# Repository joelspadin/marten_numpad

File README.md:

# Marten Numpad

Marten 22 is a wireless, 21/22 key numpad named after a [cute, woodland animal](https://en.wikipedia.org/wiki/American_marten). (There is no meaning to the name other than that I like them, and I couldn't find any existing keyboards named after them.) It is based on the nRF52840 SoC and uses a 3D printed case.

It has the following features:

- USB and Bluetooth support with [ZMK Firmware](https://zmk.dev/)
- Hot swap sockets for MX switches
- Supports Li-Ion or LiPo batteries up to 68x40x8 mm or 55x44x8 mm.
- The top-left and top-right keys can be replaced with encoders.
  - Supports [SKYLOONG keyboard knobs](https://skyloongtech.com/skyloong-keyboard-knobs/) (silicone cover versions only) or a separate encoder PCB with 3D printed case
- Any pair of two keys on the top row can be replaced with a display.
  - This uses a separate display PCB and connects with a ribbon cable.
  - nice!view and SSD1306 OLED display modules are supported.

A 22/23 key layout with a split plus key would be possible, but it would require a separate PCB from the 21/22 key layout. There is no way to fit three hot swap sockets into the space for the plus key without rotating the 1U keys 90 degrees, and this could damage keycaps, so I opted not to include that as an option.

(TODO: add renders/pictures of the completed keyboard)

> ⚠️ WARNING ⚠️ </br>
> I have received PCBs but they have not been fully tested. You should probably not make one yourself until I verify that everything works.

**Hardware status:**

| Component                | Status   |
| ------------------------ | -------- |
| Numpad PCB               | Untested |
| nice!view display module | Untested |
| OLED display module      | Untested |
| Encoder module           | Untested |
| 3D printed case          | Untested |

**Firmware status:**

| Component             | Status          |
| --------------------- | --------------- |
| Base firmware         | Not implemented |
| Numlock LED           | Not implemented |
| Custom display screen | Not implemented |
| nPM1300 charger       | Not implemented |
| nPM1300 fuel gauge    | Not implemented |
| Power button          | Not implemented |

## PCB

KiCad files for the PCBs can be found in the [pcb](./pcb) directory. There are a few PCBs:

- [numpad.kicad_pro](./pcb/numpad.kicad_pro) is the main PCB.
- [display.kicad_pro](./pcb/display.kicad_pro) is an optional daughterboard for connecting a [nice!view](https://nicekeyboards.com/nice-view/) display.
- [display_oled.kicad_pro](./pcb/display_oled.kicad_pro) is an optional daughterboard for connect an SSD1306 OLED display.
  - It works with the common SSD1306 display modules you can find from a wide variety of sellers, but make sure to get one which does _not_ have a pin header already soldered.
- [encoder.kicad_pro](./pcb/encoder.kicad_pro) is an optional daughterboard for an EC11 encoder.
- [peripheral.kicad_pro](./pcb/peripheral.kicad_pro) is template for creating your own daughterboards.

The main PCB requires a couple of parts which are not hand solderable, so PCB assembly is required.

The display and encoder PCBs are hand solderable (though the SMD parts on the encoder are difficult to solder). The encoder PCB also requires modifying the EC11 encoder by clipping its pins short.

Instructions for ordering and assembling the hardware will be found on the wiki, once I finish writing them. (TODO: add a wiki page)

[PCBWay](https://www.pcbway.com/) provided me a discount on PCB assembly in exchange for [sharing pictures of the completed board and talking about my experience ordering from them](https://github.com/joelspadin/marten_numpad/wiki/PCBWay-Assembly).

### Custom Peripherals

The numpad PCB has a [Molex 5051100692](https://www.molex.com/en-us/products/part-detail/5051100692) FFC connector (labeled "Display") which can be used to connect to a daughterboard using a 6-pin ribbon cable. It provides 3.3 V power, two ground pins, and three GPIO pins. While its main purpose is to connect a display, you can use this to add your own custom hardware as well.

(TODO: add a wiki page explaining custom hardware and firmware)

## Case

TODO

## Firmware

TODO

## Credits

- Fonts:
  - [Fredoka](https://fonts.google.com/specimen/Fredoka)
- Libraries:
  - [marbastlib](https://github.com/ebastler/marbastlib)
  - Some footprints are modified from the [KiCad Libraries](https://gitlab.com/kicad/libraries/kicad-footprints)
- 3D models
  - Some 3D models are generated using [KiCad Packages3D Generator](https://gitlab.com/kicad/libraries/kicad-packages3D-generator)
  - [128x32 OLED display](https://grabcad.com/library/0-91-128x32-oled-display-1)
  - [JST SH connector](https://grabcad.com/library/jst-sh-smd-connectors-1)
  - Models for the following parts are provided by their respective manufacturers:
    - [Bourns PEC11L](https://www.bourns.com/products/encoders/contacting-encoders/product/PEC11L)
    - [HRO TYPE-C-31-M-12](https://www.snapeda.com/parts/TYPE-C-31-M-12/HRO%20Electronics%20Co.,%20Ltd./view-part/)
    - [Kingbright APTR3216-VFX](https://www.kingbrightusa.com/product.asp?catalog_name=LED&product_id=APTR3216-VFX)
    - [Molex 781710002](https://www.molex.com/en-us/products/part-detail/781710002)
    - [Molex 5051100692](https://www.molex.com/en-us/products/part-detail/5051100692)
    - [Mill-Max 811-22-002-30-004101](https://www.mill-max.com/products/spring-loaded/pogo-pin-header-strip/811/30-004101/811-22-002-30-004101)
    - [Mill-Max 811-22-004-30-001101](https://www.mill-max.com/products/spring-loaded/pogo-pin-header-strip/811/30-001101/811-22-004-30-001101)
    - [Mill-Max 821-22-005-10-001101](https://www.mill-max.com/products/spring-loaded/pogo-pin-header-strip/821/10-001101/821-22-005-10-001101)
    - [Raytac MDBT50Q-1MV2](https://www.raytac.com/product/ins.php?index_id=24)
    - [Würth 9774005243R](https://www.we-online.com/en/components/products/SMSI_SMT_STEEL_SPACER_M2_THREAD_INTERNAL)

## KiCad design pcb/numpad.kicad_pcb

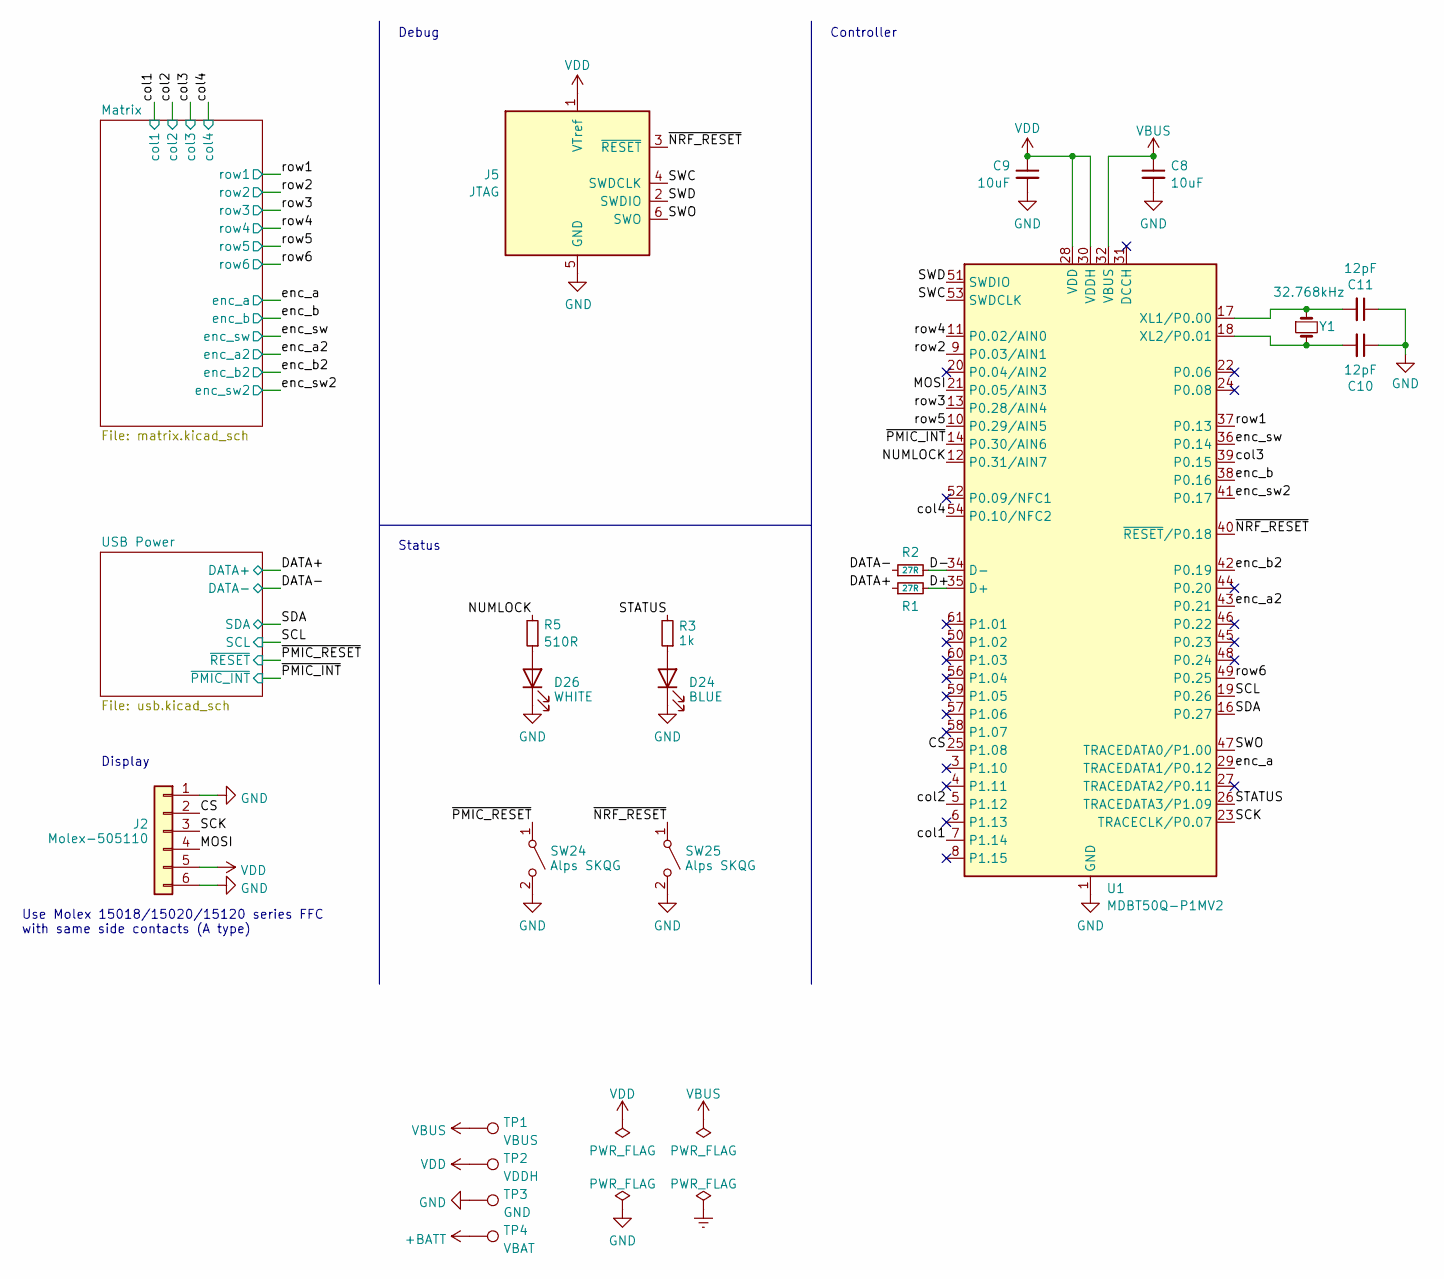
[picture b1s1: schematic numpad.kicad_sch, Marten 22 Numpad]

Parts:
C8, C9: 10uF; C_0603_1608Metric; Manufacturer Part Number GRM188Z71A106KA73D
C10, C11: 12pF; C_0402_1005Metric; Manufacturer Part Number CC0402GRNPO9BN120
D24: BLUE; LED_0603_1608Metric; Manufacturer Part Number NCD0603B5
D26: WHITE; LED_1206_3216Metric_ReverseMount_Hole2x2mm; Manufacturer Part Number MHT151WDT
J2: Molex-505110; Molex_5051100692_1x06_P0.5mm_Anchor; Manufacturer Part Number 5051100692
J5: JTAG; Tag-Connect_TC2030-IDC-NL_2x03_P1.27mm_Vertical; Manufacturer Part Number DNP
R1, R2: 27R; R_0402_1005Metric; Manufacturer Part Number RC0402FR-0727RL
R3: 1k; R_0603_1608Metric; Manufacturer Part Number FRC0603J102 TS
R5: 510R; R_0603_1608Metric; Manufacturer Part Number FRC0603J471 TS
SW24: Alps SKQG; SW_SPST_SKQG_WithStem; Manufacturer Part Number SKQGADE010
SW25: Alps SKQG; SW_SPST_SKQG_WithStem; Manufacturer Part Number SKQGABE010
TP1: VBUS; TestPoint_Pad_D1.5mm; Manufacturer Part Number DNP
TP2: VDDH; TestPoint_Pad_D1.5mm; Manufacturer Part Number DNP
TP3: GND; TestPoint_Pad_D1.5mm; Manufacturer Part Number DNP
TP4: VBAT; TestPoint_Pad_D1.5mm; Manufacturer Part Number DNP
U1: MDBT50Q-P1MV2; Raytac_MDBT50Q; Manufacturer Part Number MDBT50Q-P1MV2
Y1: 32.768kHz; Crystal_SMD_3215-2Pin_3.2x1.5mm; Manufacturer Part Number SC-32S32.768kHz20PPM9pF

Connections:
+BATT: TP4.1; also elsewhere on the board
/CS: J2.2, U1.25 (P1.08)
/D+: R1.2, U1.35 (D+)
/D-: R2.2, U1.34 (D-)
/DATA+: R1.1; also elsewhere on the board
/DATA-: R2.1; also elsewhere on the board
/MOSI: J2.4, U1.21 (P0.05/AIN3)
/NUMLOCK: R5.2, U1.12 (P0.31/AIN7)
/SCK: J2.3, U1.23 (TRACECLK/P0.07)
/SCL: U1.19 (P0.26); also elsewhere on the board
/SDA: U1.16 (P0.27); also elsewhere on the board
/STATUS: R3.2, U1.26 (TRACEDATA3/P1.09)
/SWC: J5.4 (SWDCLK), U1.53 (SWDCLK)
/SWD: J5.2 (SWDIO), U1.51 (SWDIO)
/SWO: J5.6 (SWO), U1.47 (TRACEDATA0/P1.00)
/col1: U1.7 (P1.14); also elsewhere on the board
/col2: U1.5 (P1.12); also elsewhere on the board
/col3: U1.39 (P0.15); also elsewhere on the board
/col4: U1.54 (P0.10/NFC2); also elsewhere on the board
/enc_a: U1.29 (TRACEDATA1/P0.12); also elsewhere on the board
/enc_a2: U1.43 (P0.21); also elsewhere on the board
/enc_b: U1.38 (P0.16); also elsewhere on the board
/enc_b2: U1.42 (P0.19); also elsewhere on the board
/enc_sw: U1.36 (P0.14); also elsewhere on the board
/enc_sw2: U1.41 (P0.17); also elsewhere on the board
/row1: U1.37 (P0.13); also elsewhere on the board
/row2: U1.9 (P0.03/AIN1); also elsewhere on the board
/row3: U1.13 (P0.28/AIN4); also elsewhere on the board
/row4: U1.11 (P0.02/AIN0); also elsewhere on the board
/row5: U1.10 (P0.29/AIN5); also elsewhere on the board
/row6: U1.49 (P0.25); also elsewhere on the board
/~NRF_RESET: J5.3 (~RESET), SW25.1 (A), U1.40 (~RESET/P0.18)
/~PMIC_INT: U1.14 (P0.30/AIN6); also elsewhere on the board
/~PMIC_RESET: SW24.1 (A); also elsewhere on the board
GND: C8.2, C9.2, C10.1, C11.1, D24.1 (K), D26.1 (K), J2.1, J2.6, J5.5 (GND), SW24.2 (B), SW25.2 (B), TP3.1, U1.1 (GND), U1.2 (GND), U1.15 (GND), U1.33 (GND), U1.55 (GND); also elsewhere on the board
unnamed: D24.2 (A), R3.1
unnamed: D26.2 (A), R5.1
unnamed: C11.2, U1.17 (XL1/P0.00), Y1.1
unnamed: C10.2, U1.18 (XL2/P0.01), Y1.2
VBUS: C8.1, TP1.1, U1.32 (VBUS); also elsewhere on the board
VDD: C9.1, J2.5, J5.1 (VTref), TP2.1, U1.28 (VDD), U1.30 (VDDH); also elsewhere on the board

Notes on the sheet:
Display
Controller
Debug
Use Molex 15018/15020/15120 series FFC with same side contacts (A type)
Status

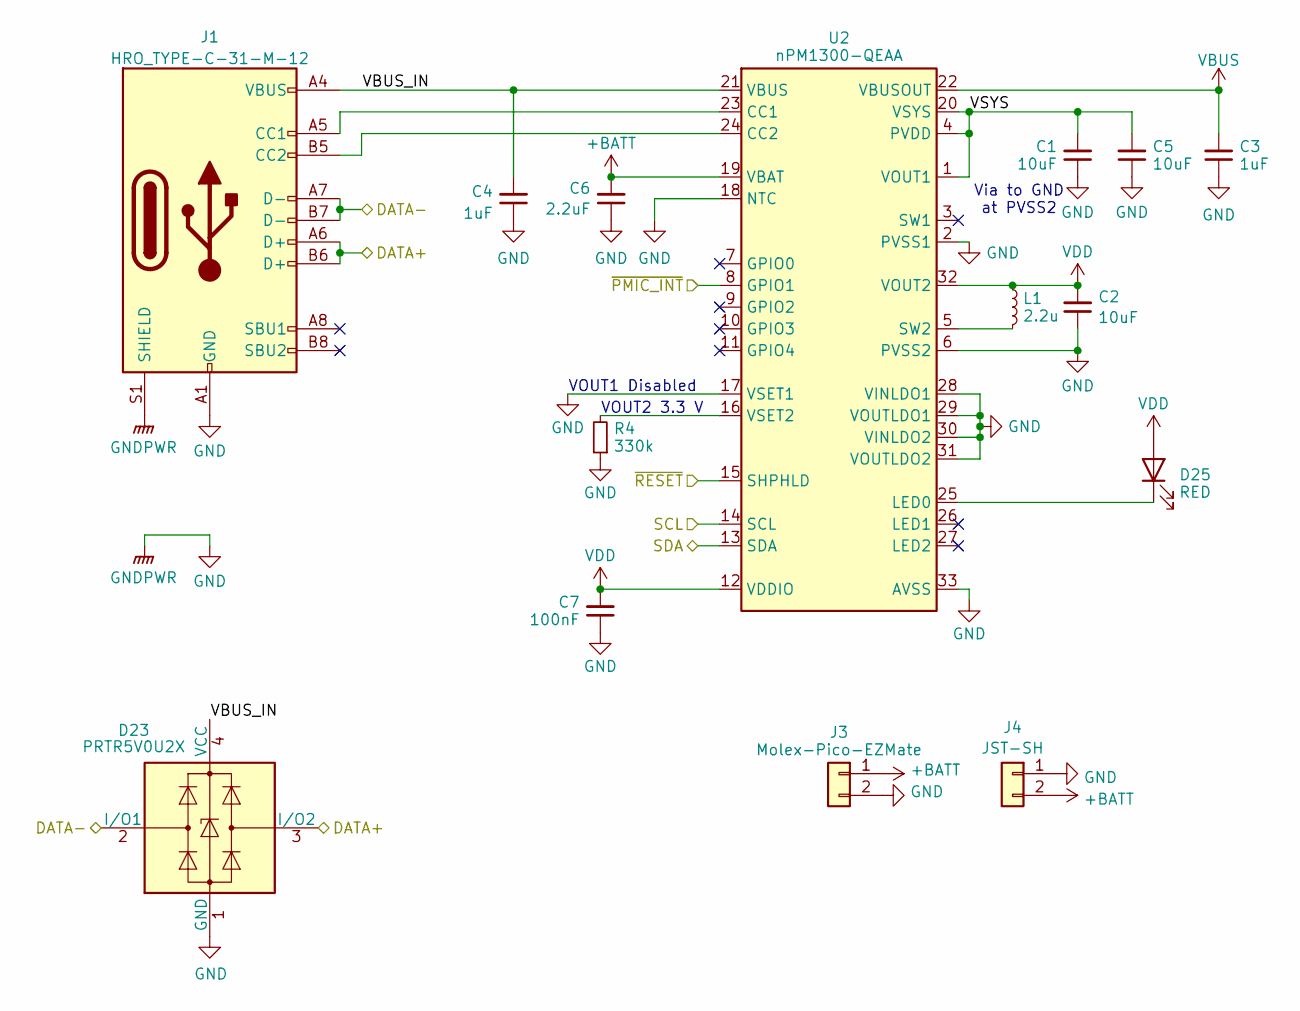
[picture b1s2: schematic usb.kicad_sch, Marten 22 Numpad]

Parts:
C1, C2, C5: 10uF; C_0603_1608Metric; Manufacturer Part Number 0603X106M250NT
C3, C4: 1uF; C_0603_1608Metric; Manufacturer Part Number 0603X105K100NT
C6: 2.2uF; C_0603_1608Metric; Manufacturer Part Number TCC0603X5R225K250CT
C7: 100nF; C_0402_1005Metric; Manufacturer Part Number TCC0402X5R104K250AT
D23: PRTR5V0U2X; SOT-143; Manufacturer Part Number PRTR5V0U2X,215
D25: RED; LED_0603_1608Metric; Manufacturer Part Number NCD0603R6
J1: HRO_TYPE-C-31-M-12; USB_C_Receptacle_HRO_TYPE-C-31-M-12; Manufacturer Part Number TYPE-C-31-M-12
J3: Molex-Pico-EZMate; Molex_Pico-EZmate_78171-0002_1x02-1MP_P1.20mm_Vertical; Manufacturer Part Number 781710002
J4: JST-SH; JST_SH_SM02B-SRSS-TB_1x02-1MP_P1.00mm_Horizontal_Anchor; Manufacturer Part Number SM02B-SRSS-TB
L1: 2.2u; L_0805_2012Metric; Manufacturer Part Number MLZ2012M2R2HT000
R4: 330k; R_0402_1005Metric; Manufacturer Part Number RC0402FR-07330KL
U2: nPM1300-QEAA; QFN-32-1EP_5x5mm_P0.5mm_EP3.5x3.5mm_ThermalVias; Manufacturer Part Number nPM1300-QEAA

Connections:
+BATT: C6.2, J3.1, J4.2, U2.19 (VBAT); also elsewhere on the board
/DATA+: D23.3 (I/O2), J1.A6 (D+), J1.B6 (D+); also elsewhere on the board
/DATA-: D23.2 (I/O1), J1.A7 (D-), J1.B7 (D-); also elsewhere on the board
/SCL: U2.14 (SCL); also elsewhere on the board
/SDA: U2.13 (SDA); also elsewhere on the board
/USB Power/VBUS_IN: C4.2, D23.4 (VCC), J1.A4 (VBUS), J1.A9 (VBUS), J1.B4 (VBUS), J1.B9 (VBUS), U2.21 (VBUS)
/USB Power/VSYS: C1.2, C5.2, U2.1 (VOUT1), U2.4 (PVDD), U2.20 (VSYS)
/~PMIC_INT: U2.8 (GPIO1); also elsewhere on the board
/~PMIC_RESET: U2.15 (SHPHLD); also elsewhere on the board
GND: C1.1, C2.1, C3.1, C4.1, C5.1, C6.1, C7.1, D23.1 (GND), J1.A1 (GND), J1.A12 (GND), J1.B1 (GND), J1.B12 (GND), J1.S1 (SHIELD), J3.2, J4.1, R4.1, U2.2 (PVSS1), U2.6 (PVSS2), U2.17 (VSET1), U2.18 (NTC), U2.28 (VINLDO1), U2.29 (VOUTLDO1), U2.30 (VINLDO2), U2.31 (VOUTLDO2), U2.33 (AVSS); also elsewhere on the board
unnamed: D25.1 (K), U2.25 (LED0)
unnamed: J1.A5 (CC1), U2.23 (CC1)
unnamed: J1.B5 (CC2), U2.24 (CC2)
unnamed: L1.2, U2.5 (SW2)
unnamed: R4.2, U2.16 (VSET2)
VBUS: C3.2, U2.22 (VBUSOUT); also elsewhere on the board
VDD: C2.2, C7.2, D25.2 (A), L1.1, U2.12 (VDDIO), U2.32 (VOUT2); also elsewhere on the board

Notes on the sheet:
VOUT1 Disabled
Via to GND at PVSS2
VOUT2 3.3 V

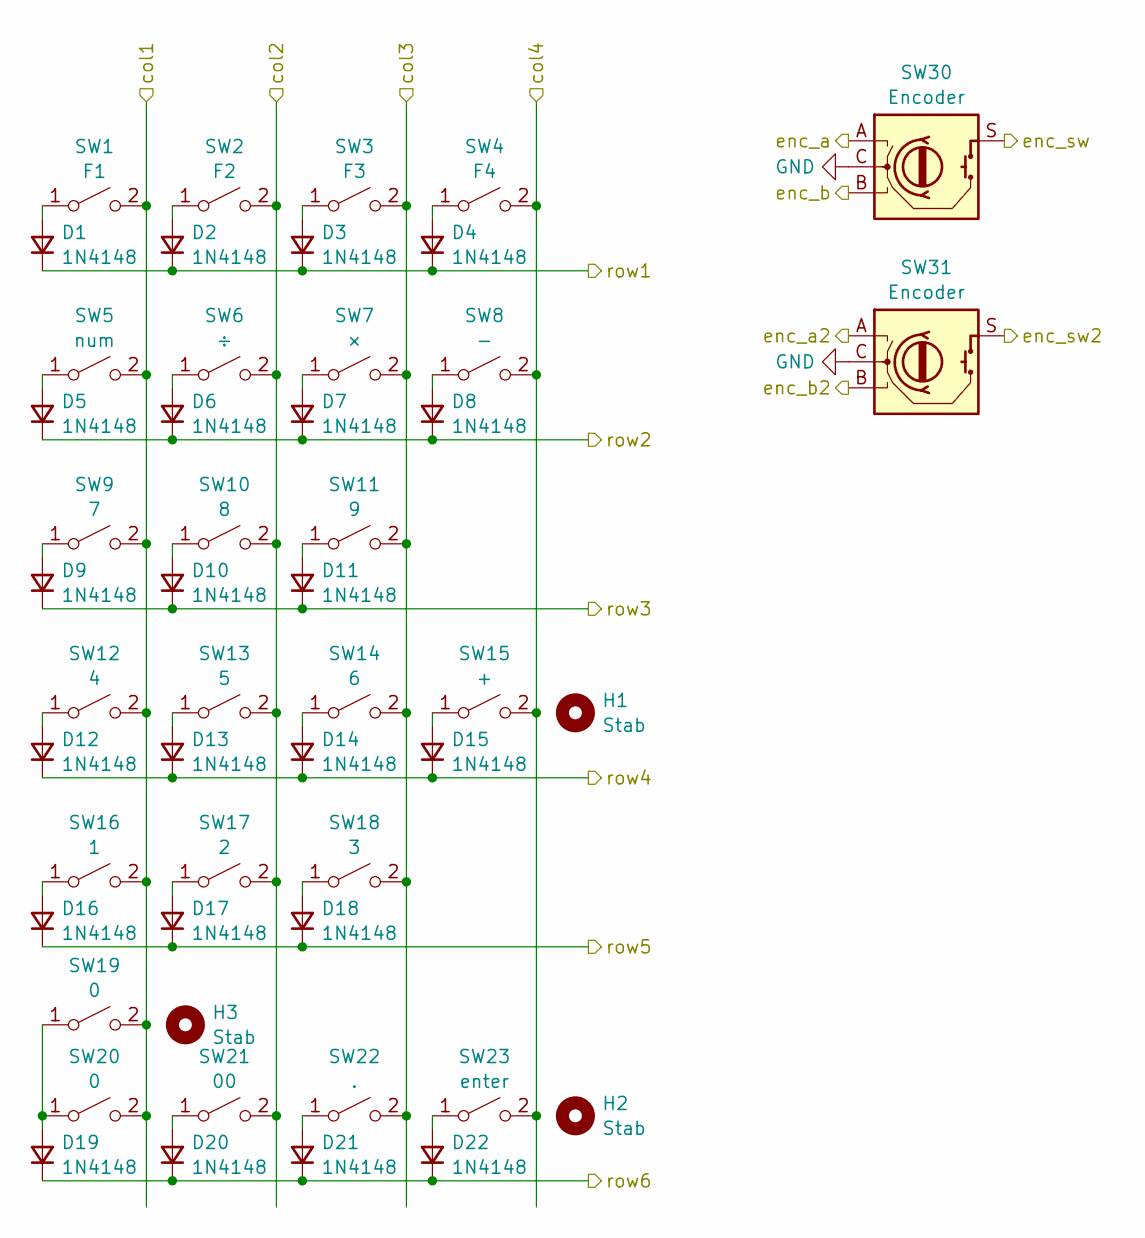
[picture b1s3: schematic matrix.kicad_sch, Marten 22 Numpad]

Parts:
D1, D2, D3, D4, D5, D6, D7, D8, D9, D10, D11, D12, D13, D14, D15, D16, D17, D18, D19, D20, D21, D22: 1N4148; D_SOD-523; Manufacturer Part Number 1N4148WT
H1, H2, H3: Stab; STAB_MX_2u; Manufacturer Part Number DNP
SW1: F1; SW_MX_HS_CPG151101S11_1u; Manufacturer Part Number CPG151101S11-16
SW2: F2; SW_MX_HS_CPG151101S11_1u; Manufacturer Part Number CPG151101S11-16
SW3: F3; SW_MX_HS_CPG151101S11_1u; Manufacturer Part Number CPG151101S11-16
SW4: F4; SW_MX_HS_CPG151101S11_1u; Manufacturer Part Number CPG151101S11-16
SW5: num; SW_MX_HS_CPG151101S11_1u; Manufacturer Part Number CPG151101S11-16
SW6: ÷; SW_MX_HS_CPG151101S11_1u; Manufacturer Part Number CPG151101S11-16
SW7: ×; SW_MX_HS_CPG151101S11_1u; Manufacturer Part Number CPG151101S11-16
SW8: −; SW_MX_HS_CPG151101S11_1u; Manufacturer Part Number CPG151101S11-16
SW9: 7; SW_MX_HS_CPG151101S11_1u; Manufacturer Part Number CPG151101S11-16
SW10: 8; SW_MX_HS_CPG151101S11_1u; Manufacturer Part Number CPG151101S11-16
SW11: 9; SW_MX_HS_CPG151101S11_1u; Manufacturer Part Number CPG151101S11-16
SW12: 4; SW_MX_HS_CPG151101S11_1u; Manufacturer Part Number CPG151101S11-16
SW13: 5; SW_MX_HS_CPG151101S11_1u; Manufacturer Part Number CPG151101S11-16
SW14: 6; SW_MX_HS_CPG151101S11_1u; Manufacturer Part Number CPG151101S11-16
SW15: +; SW_MX_HS_CPG151101S11_1u; Manufacturer Part Number CPG151101S11-16
SW16: 1; SW_MX_HS_CPG151101S11_1u; Manufacturer Part Number CPG151101S11-16
SW17: 2; SW_MX_HS_CPG151101S11_1u; Manufacturer Part Number CPG151101S11-16
SW18: 3; SW_MX_HS_CPG151101S11_1u; Manufacturer Part Number CPG151101S11-16
SW19, SW20: 0; SW_MX_HS_CPG151101S11_1u; Manufacturer Part Number CPG151101S11-16
SW21: 00; SW_MX_HS_CPG151101S11_1u; Manufacturer Part Number CPG151101S11-16
SW22: .; SW_MX_HS_CPG151101S11_1u; Manufacturer Part Number CPG151101S11-16
SW23: enter; SW_MX_HS_CPG151101S11_1u; Manufacturer Part Number CPG151101S11-16
SW30, SW31: Encoder; Skyloong_Knob_Pads; Manufacturer Part Number DNP

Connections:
/col1: SW1.2 (B), SW5.2 (B), SW9.2 (B), SW12.2 (B), SW16.2 (B), SW19.2 (B), SW20.2 (B); also elsewhere on the board
/col2: SW2.2 (B), SW6.2 (B), SW10.2 (B), SW13.2 (B), SW17.2 (B), SW21.2 (B); also elsewhere on the board
/col3: SW3.2 (B), SW7.2 (B), SW11.2 (B), SW14.2 (B), SW18.2 (B), SW22.2 (B); also elsewhere on the board
/col4: SW4.2 (B), SW8.2 (B), SW15.2 (B), SW23.2 (B); also elsewhere on the board
/enc_a: SW30.A; also elsewhere on the board
/enc_a2: SW31.A; also elsewhere on the board
/enc_b: SW30.B; also elsewhere on the board
/enc_b2: SW31.B; also elsewhere on the board
/enc_sw: SW30.S; also elsewhere on the board
/enc_sw2: SW31.S; also elsewhere on the board
/row1: D1.1 (K), D2.1 (K), D3.1 (K), D4.1 (K); also elsewhere on the board
/row2: D5.1 (K), D6.1 (K), D7.1 (K), D8.1 (K); also elsewhere on the board
/row3: D9.1 (K), D10.1 (K), D11.1 (K); also elsewhere on the board
/row4: D12.1 (K), D13.1 (K), D14.1 (K), D15.1 (K); also elsewhere on the board
/row5: D16.1 (K), D17.1 (K), D18.1 (K); also elsewhere on the board
/row6: D19.1 (K), D20.1 (K), D21.1 (K), D22.1 (K); also elsewhere on the board
GND: SW30.C, SW31.C; also elsewhere on the board
unnamed: D1.2 (A), SW1.1 (A)
unnamed: D2.2 (A), SW2.1 (A)
unnamed: D3.2 (A), SW3.1 (A)
unnamed: D4.2 (A), SW4.1 (A)
unnamed: D5.2 (A), SW5.1 (A)
unnamed: D6.2 (A), SW6.1 (A)
unnamed: D7.2 (A), SW7.1 (A)
unnamed: D8.2 (A), SW8.1 (A)
unnamed: D9.2 (A), SW9.1 (A)
unnamed: D10.2 (A), SW10.1 (A)
unnamed: D11.2 (A), SW11.1 (A)
unnamed: D12.2 (A), SW12.1 (A)
unnamed: D13.2 (A), SW13.1 (A)
unnamed: D14.2 (A), SW14.1 (A)
unnamed: D15.2 (A), SW15.1 (A)
unnamed: D16.2 (A), SW16.1 (A)
unnamed: D17.2 (A), SW17.1 (A)
unnamed: D18.2 (A), SW18.1 (A)
unnamed: D19.2 (A), SW19.1 (A), SW20.1 (A)
unnamed: D20.2 (A), SW21.1 (A)
unnamed: D21.2 (A), SW22.1 (A)
unnamed: D22.2 (A), SW23.1 (A)

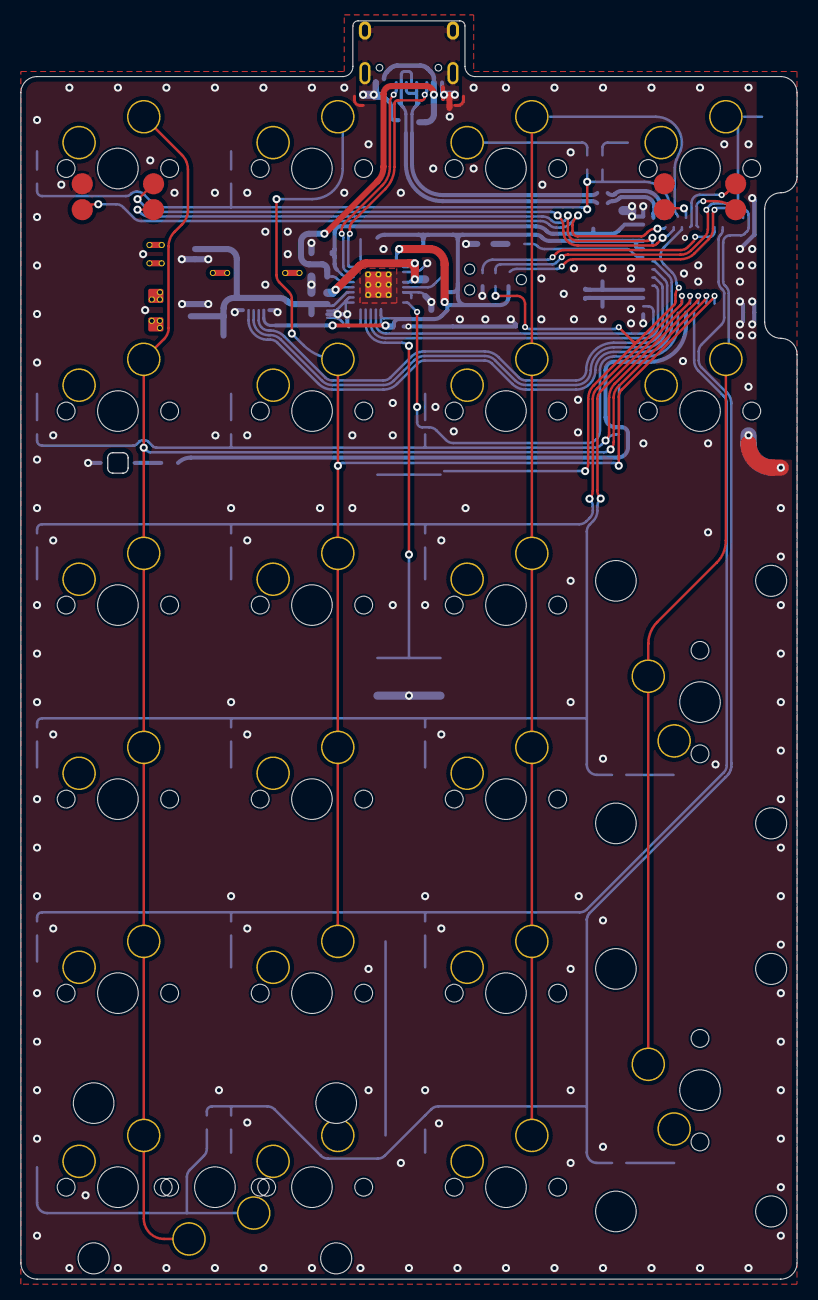
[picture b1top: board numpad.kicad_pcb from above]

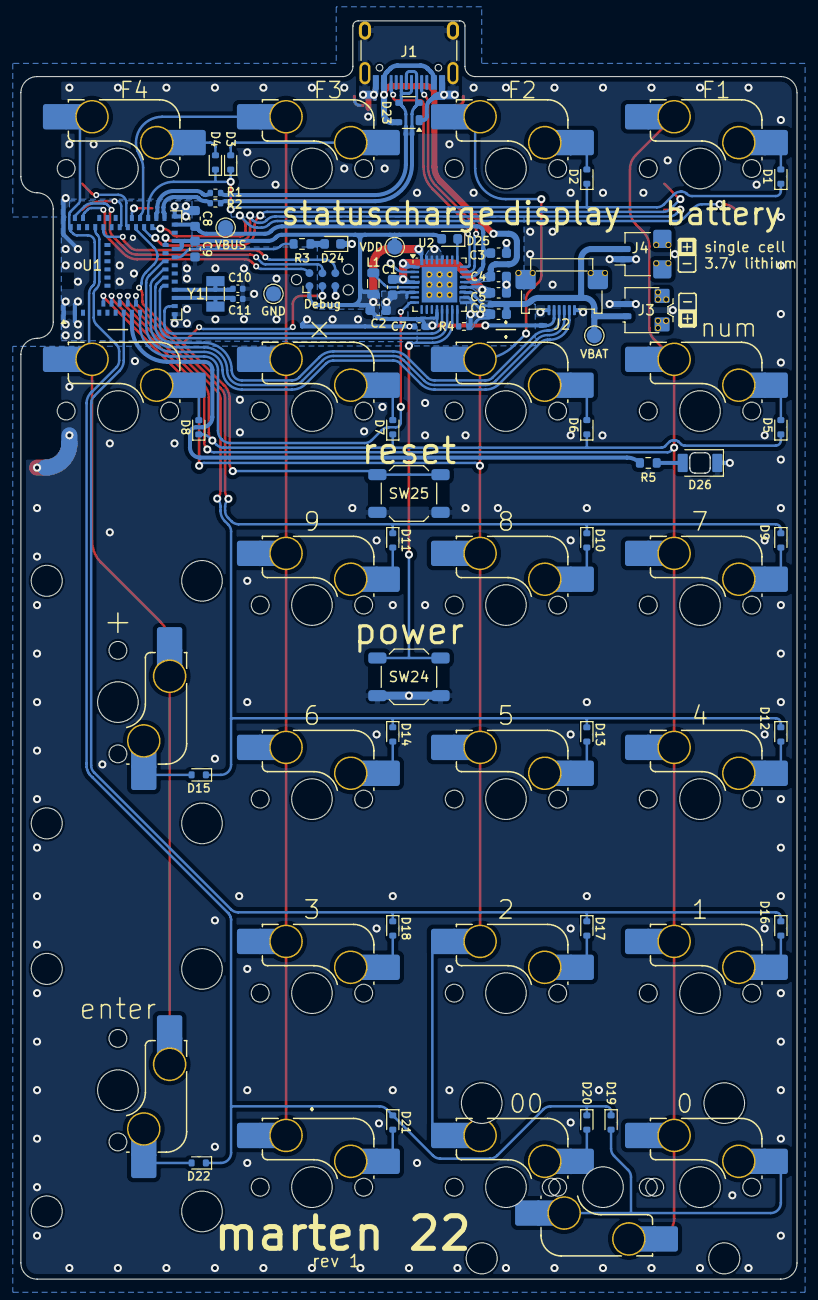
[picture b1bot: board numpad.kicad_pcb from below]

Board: 2 copper layers, 76.2 x 123.5 mm, 85 parts (81 on the bottom side), 70 nets.

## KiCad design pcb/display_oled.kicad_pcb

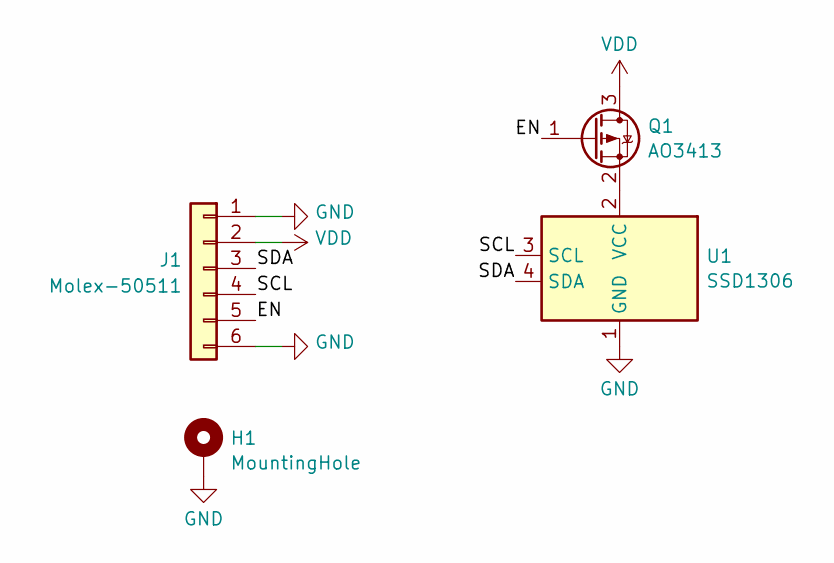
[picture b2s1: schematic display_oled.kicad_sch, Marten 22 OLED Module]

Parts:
H1: MountingHole; MountingHole_2.2mm_M2_Pad_Via; Manufacturer Part Number DNP
J1: Molex-50511; Molex_5051100692_1x06_P0.5mm_Anchor_2; Manufacturer Part Number 5051100692
Q1: AO3413; SOT-23-3
U1: SSD1306; SSD1306_Pogo_Pin; Manufacturer Part Number 821-22-005-10-000101

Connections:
/EN: J1.5, Q1.1 (G)
/SCL: J1.4, U1.3 (SCL)
/SDA: J1.3, U1.4 (SDA)
GND: H1.1, J1.1, J1.6, U1.1 (GND)
unnamed: Q1.2 (S), U1.2 (VCC)
VDD: J1.2, Q1.3 (D)

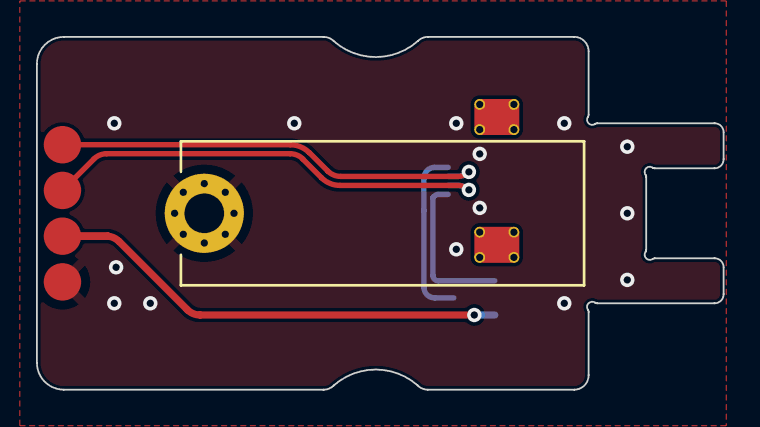
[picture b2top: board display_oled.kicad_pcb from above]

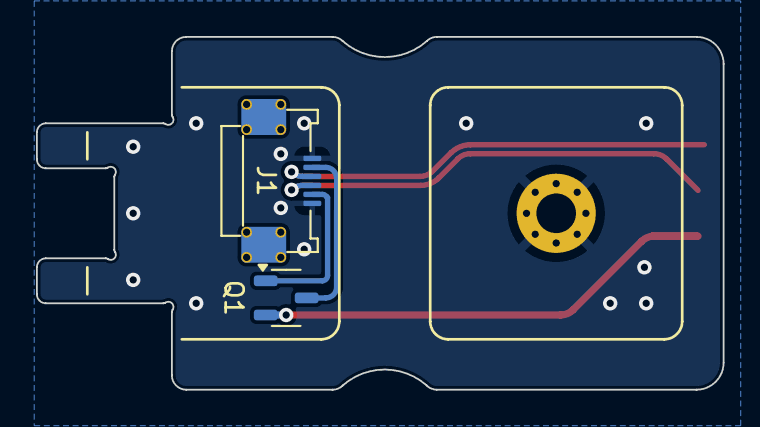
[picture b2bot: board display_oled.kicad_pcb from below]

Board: 2 copper layers, 38.1 x 19.6 mm, 4 parts (2 on the bottom side), 6 nets.

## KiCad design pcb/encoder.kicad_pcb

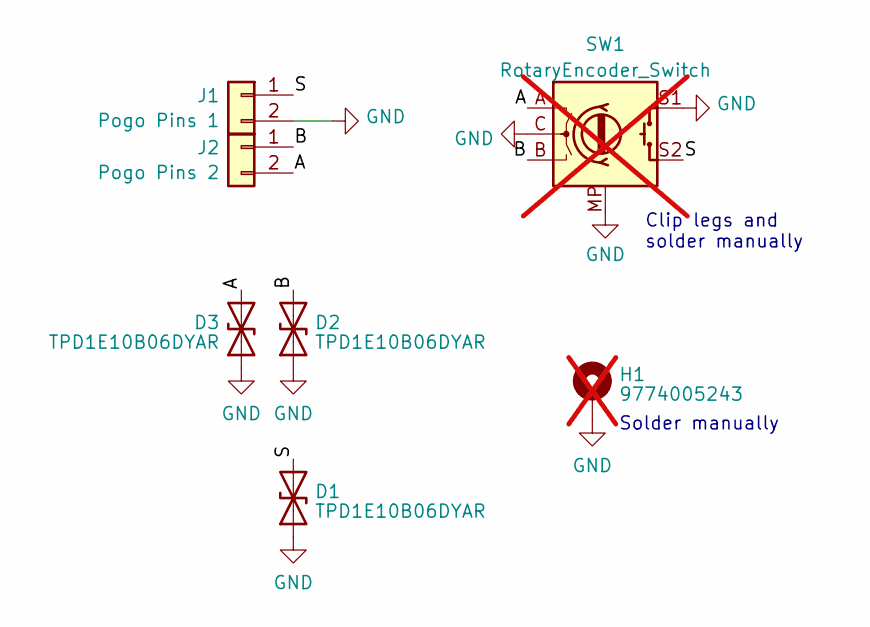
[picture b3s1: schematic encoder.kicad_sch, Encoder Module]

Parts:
D1, D2, D3: TPD1E10B06DYAR; D_SOD-523; Manufacturer Part Number TPD1E10B06DYAR
H1: 9774005243; Wurth_9774005243; Manufacturer Part Number 9774005243R; not fitted
J1: Pogo Pins 1; Mill-Max_811-22-002-03-004101; Manufacturer Part Number 811-22-002-30-004101
J2: Pogo Pins 2; Mill-Max_811-22-002-03-004101; Manufacturer Part Number 811-22-002-30-004101
SW1: RotaryEncoder_Switch; Bourns_PEC11L-Switch; Manufacturer Part Number PEC11L-4115F-S0020; not fitted

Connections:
/A: D3.2 (A2), J2.2, SW1.A
/B: D2.2 (A2), J2.1, SW1.B
/S: D1.2 (A2), J1.1, SW1.S2
GND: D1.1 (A1), D2.1 (A1), D3.1 (A1), H1.1, J1.2, SW1.C, SW1.MP, SW1.S1

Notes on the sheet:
Solder manually
Clip legs and solder manually

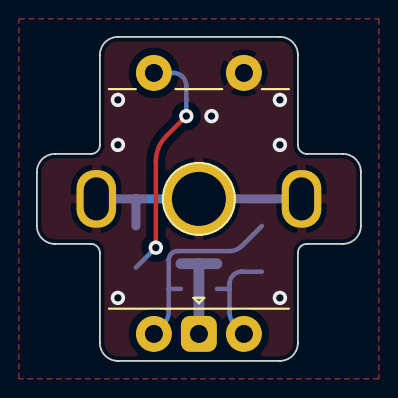
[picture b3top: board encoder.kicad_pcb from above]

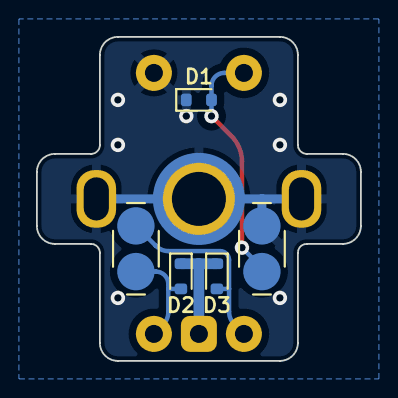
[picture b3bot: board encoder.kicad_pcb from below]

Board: 2 copper layers, 18.0 x 18.0 mm, 7 parts (6 on the bottom side), 4 nets.

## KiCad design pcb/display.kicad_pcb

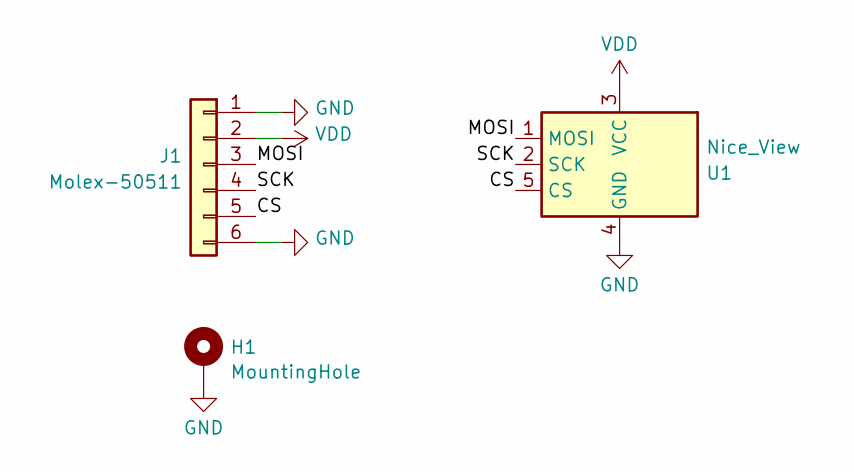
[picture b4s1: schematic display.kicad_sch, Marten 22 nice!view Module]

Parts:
H1: MountingHole; MountingHole_2.2mm_M2_Pad_Via; Manufacturer Part Number DNP
J1: Molex-50511; Molex_5051100692_1x06_P0.5mm_Anchor_2; Manufacturer Part Number 505110069
U1: Nice_View; Nice_View_Pogo_pin; Manufacturer Part Number 821-22-005-10-000101

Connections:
/CS: J1.5, U1.5 (CS)
/MOSI: J1.3, U1.1 (MOSI)
/SCK: J1.4, U1.2 (SCK)
GND: H1.1, J1.1, J1.6, U1.4 (GND)
VDD: J1.2, U1.3 (VCC)

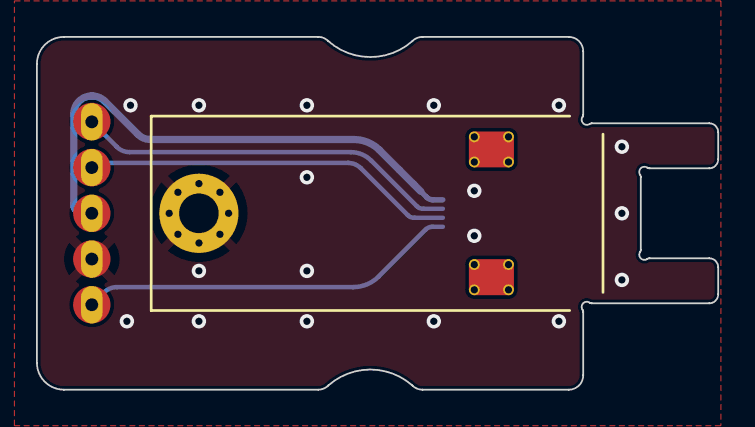
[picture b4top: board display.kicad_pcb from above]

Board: 2 copper layers, 37.8 x 19.6 mm, 3 parts (1 on the bottom side), 5 nets.

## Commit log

2024-10-14 Reorganize repo and start clean history
    Restarting the history of the repo to avoid bloating it with old fonts
    and 3D models that I ended up not using.
2024-10-14 Use KiCad SOT-23-3 footprint
    The copied footprint was likely due to a missing 3D model, but the
    current KiCad library has a 3D model now.
2024-11-03 Fix BOM and update DRC exclusions
2024-11-08 Add Molex connector to peripheral template
2024-11-08 Use switch requiring less force for reset/power
2024-11-08 Add an initial readme
